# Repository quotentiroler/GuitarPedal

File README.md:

## Resurrected random guitar pedal project

This is a resurrected version of my old guitar pedal project: a digital
guitar pedal built around an RP2354A and a TI audio codec, with all the
effects done in software on a core of its own.

It went through a phase with a little OLED screen and a couple of rotary
encoders on it, and that's gone now.  Editing seventeen effects through a
128x128 screen and two knobs was never going to be pleasant, and I'm not
exactly known for my mad UI designing skillz, so the pedal itself is down
to one knob and one stomp switch and the deep editing happens somewhere
that already has a screen: there's a web app that talks to it over USB
MIDI from a browser.

So what's in here:

 - `Hardware` has the kicad files.
 - `Effects` has the seventeen effects, one file each.  They are up here
   rather than inside the firmware because three different things are
   built from them: the firmware, the test bench, and the web app's
   controls.
 - `Audio` has the DSP the effects are built out of - biquads, envelope
   followers, LFOs - and the audio loop itself.  The bench compiles the
   same files, so what gets measured is the pedal's own arithmetic.
 - `Firmware` is the rest of what runs on the pedal: USB, MIDI, scenes,
   the board pin maps.
 - `WebMIDI` is the web app that edits it.
 - `scripts` is what the build runs - the effect generator, the math
   tables, and the checks that refuse a firmware image doing something
   the audio core shouldn't.
 - `Validation` is the test suite.  Some of it runs on your machine and
   some of it wants a pedal plugged in.
 - `Documentation` remains a very optimistic name for a directory.

## Firmware

I've only ever built the firmware on Linux, but it *should* be perfectly
possible to build on MacOS or Windows too if you just figure out the
platform requirements. The project depends on the `pico-sdk` and
`tinyusb` libraries, and has submodules for both, so they get built
automatically, but the build tools your platform has to provide.

Regardless of platform, you'll need the basics:
 - git
 - make
 - python3
 - cmake

and a 32-bit arm cross-build environment.  On Linux, that would be
something like
 - arm-none-eabi-binutils-cs
 - arm-none-eabi-gcc-cs
 - arm-none-eabi-newlib

There's more than one board this can be built for, and the build won't
guess.  You say which one this tree is about once, in
`board.local`, and it stays said - it's a file rather than a
cmake cache variable specifically so that blowing away `build/` doesn't
silently change your mind for you.  So:
```
	git clone https://github.com/torvalds/GuitarPedal.git
	cd GuitarPedal
	echo unified > board.local
	make prep
	make
```
`unified` is the current one-board pedal.  The other is `split`, which is
the older modular pair of boards.  If you forget this step the configure
will stop and tell you, which is the intended behaviour - a wrong board
should be an error you fix once, not a working build for hardware you
don't have.

That gets you `build/pedal-unified.uf2` (and `.elf`, and `.bin`).  Every
artifact is named for the board it's for, so there is deliberately no
`pedal.uf2` to grab by mistake.  You can build the other board without
changing what the tree is about - ``make split`` - or both with ``make
all-boards``.

To get the `.uf2` onto the pedal you need it in BOOTSEL mode, and there
are two ways.  If it's running and plugged in, send it MIDI CC 20 with
value 126 and it will reboot into BOOTSEL on its own:
```
	amidi -l                          # find which card the pedal is
	amidi -p hw:5,0 -S "B0 14 7E"     # ...and that 5 is mine, not yours
```
Otherwise, hold the knob in while you plug it in.  The rotary encoder's
switch doubles as BOOTSEL on this board - through a Schottky, so that
QSPI traffic can't fake pulling it low - and that's the route that still
works on a pedal too broken to enumerate.  The older boards had a proper
BOOTSEL button, but it was on the little MCU daughtercard, which is fine
on a bench and useless the moment the thing is screwed into a box.

Either way a USB mass storage device shows up and you copy the file to
it.

If you have installed picotool with USB support (the pico-sdk build only
builds a cut-down version without it), you can skip all that and just do
``make flash``, which builds and flashes the board in `board.local`.
``make flash-split`` does the other one.

### Testing

`Validation` has the test suite, and it's split by what it needs.

``make check`` runs the part that needs no hardware at all: the MIDI
packetiser, whether the web app still loads and still draws the right
conclusions, and a sweep that asks every biquad in the pedal where it
actually landed.  ``make check-biquad`` is that last one on its own, and
``make check-effects`` puts signals through the effects themselves.

That last one works because of `Validation/bench`, which builds the
pedal's actual audio core - the same `single_sample()`, the same effect
headers, the same compiler flags - as a program on your machine that
takes float samples on stdin and hands them back on stdout.  It is not a
model of the signal path.  It's the signal path, with the two register
blocks the audio core touches replaced by ordinary memory.

``make check-analysis`` is the other host-only one, and it is what keeps
the per-effect pages under `Documentation/effects` honest: every curve on
those pages is a measurement, and this re-measures and says when one has
stopped being true.  It is separate from ``check`` because it re-runs
every sweep on every page, which is slow.

Then there are the ones that want hardware: ``make check-hw`` with a
signal generator, ``make check-analog`` with a patch cable from the
pedal's output back to its own input, ``make check-bench`` to ask whether
a real board agrees with the host build, and ``make check-loop`` if you
have two pedals to patch into each other.

`Validation/diagnose.py` is the odd one out, because it measures
something that isn't the pedal.  With an analog pedal in the loop it asks
which *component* of that pedal disagrees with the netlist in
`Validation/spice`, rather than only that something does - every
single-component fault the netlist could have is simulated, and the one
that best explains the measurement wins.  The ranking is
[netfault](https://github.com/quotentiroler/netfault), which has to be
installed separately; the method is a fault dictionary and is older than
any of this, the survey being Bandler and Salama, Proc. IEEE 73 (1985).

It asks at several drive levels rather than sweeping once.  [RAT]'s clamp
is a logarithm, so the part that decides where it folds does nothing at
all until the drive reaches it, and a single sweep cannot tell a wrong
one from a right one - it ranks on the noise instead and does not say so.
That costs what it sounds like: an ngspice transient is about 1.8s, so a
dictionary over the whole netlist is a couple of hours.  It is built once
for a board and matched in milliseconds after that.

Nothing here has been run against a physical board yet.  Every number it
has produced so far came from a fault injected into the netlist and
handed back to it, which says the arithmetic works and says nothing about
whether a real measurement is clean enough.

## Hardware

The kicad design files (and some supporting infrastructure, like the 3D
printed insert and the enclosure drill rules) are in the ``Hardware``
subdirectory.

These days it's just the one board.  `Hardware/usb-stomp` has the RP2354A
and the TI TAC5242 codec sitting directly on it, and that's the whole
pedal: no cable, no daughtercards, no connectors in between.

What's on it:

 - a 1/4" input jack and a 1/4" output jack
 - a third 1/4" jack for an expression pedal or a remote stomp switch
 - MIDI in and out, on 3.5mm "Type A" TRS jacks (out through a 5V
   buffer, in through an optocoupler, like MIDI has always wanted)
 - USB-C, and the usual 9V guitar pedal power jack
 - one rotary encoder with a switch under it, and one stomp switch
 - three addressable WS2812B LEDs

The MIDI jacks and the expression jack are the genuinely new things.  The
older boards had nowhere to put them - the expression jack in particular
wants two ADC pins, and those are exactly the pins the old MCU board was
spending on hardware MIDI, so it could not have existed there at all.

Fair warning on that expression jack, though: the hardware is done and
the firmware can read it, but only when the host asks it to over SysEx.
Right now it's a probe for figuring out what people actually plug in
there - expression pedals don't even agree on which contact is the wiper
- and nothing is wired up to *do* anything with the result yet.

### How it used to be

It used to be modular, and those board files are all still here.  There
were two little daughtercards for the "core" hardware - the RP2354
microcontroller (`Hardware/rp2354`) and the TI TAC5112 codec
(`Hardware/codec`) - plus a board for the audio and 9V DC power jacks
(`Hardware/audio-jacks`), and a main board (`Hardware/pedal-board`) for
the pedal IO: i2c connector for the screen, USB-C programming port,
rotary encoders, pin header for stomp switches.  The two halves were
joined by a 12P 0.5mm FFC cable carrying power and data lines (i2c for
control, i2s for audio).

That was mostly so I could try out different form factors.  It let me lay
the two halves out independently, and it was flexible enough to cram a
125B enclosure full of jacks, rotaries and the screen all in one top
area.  There was also a worry about noise isolation, which in the end
never had to be tested.

I used the nice HiRose BM28 series connectors on the modular boards.
They are absolutely tiny, which makes for a great board footprint but
admittedly also makes for a slightly more complicated board due to the
tiny 0.35mm pitch.  I'm not a fan of the traditional pin headers simply
because they make it so hard to do compact form factors.

Those boards are finished and they still work - the firmware builds for
them, and they're still useful for testing.  But what this section used
to say was that if you know what you want, you should just put the codec
directly on the audio jack board and the rp2354 on the IO board.  Which,
yes.  That's the board above.

### Images

The bare `usb-stomp` board, powered up.

## Basic UI

There's no screen.  The pedal has one knob, one footswitch and three
LEDs, and everything else happens in a browser.

### On the pedal

Out of the box the footswitch is bypass - tap for in-circuit or not, hold
it for the tuner - and the knob is the master volume, with either kind of
press on it putting the volume back where it started.  That last one
sounds trivial and isn't: it's the way back when you can't see anything.

But none of that is compiled in.  There are five gestures - turn the
knob, tap it, hold it, tap the switch, hold the switch - and what each
one means is a table the pedal looks up and the app writes.  You can
point the knob at any parameter of any effect, or make a single press
take one effect's mix up while it takes another's down.  A pedal with no
screen can't tell you what its knob is for, so that has to be settable
from something that can.

The three LEDs, left to right: something is wrong (red for clipping,
amber for dropped samples), in circuit or bypassed, and the chain is
busy - where "busy" means whatever the effect thinks it means, so the
gate lights it while it's gating and the compressor while it's
compressing.

### In the browser

`WebMIDI` is a static web page that talks to the pedal over USB
MIDI.  There's nothing to install and it runs off a phone.

It doesn't know what the effects are.  It asks.  The pedal describes
every effect it has - every pot, the ranges, the units, the hover text -
and the app builds itself out of that, so it can't drift out of step with
the firmware, and adding an effect to the pedal makes it show up in the
app without touching the app.

What you actually do there is *route*.  There are seventeen effects and
none of them are in your signal path until you say so: routing picks
which ones run, and in what order, and the order is yours, because a
boost in front of a delay is a different pedal from a delay in front of a
boost.  Whatever you don't route costs nothing.

Pots are mostly just numbers, except where they aren't - the tone stacks,
the parametric EQ and the cab sim draw their actual frequency response,
so you can see the curve instead of inferring it from three knob
positions.

A tone stack with a 10dB mid bump at 810Hz and a tape echo behind it, and
the fifteen effects that aren't routed sitting at the bottom waiting to
be.  The faint grey line is the phase response.

Eight scenes fit in the pedal's own flash.  A scene is a routing plus
everything set inside it, and a MIDI program change recalls one, which is
half of what those MIDI jacks are for: a cheap footswitch can step
between scenes with no computer in sight.

## Audio effects

Seventeen of them, plus three that are always there and can't be
unrouted: the **Signal Chain** at the front, which is the input trim, the
noise gate and the master volume
([measured](Documentation/effects/signal-chain.md)), and behind them the
**Settings**, which is USB audio routing, MIDI channel, LED brightness
and what the tuner is tuning to, and the **Expression Jack**, which is
what is plugged into it and where that thing's travel ends.

They're listed in the order they run in by default.  This is an overview
and not documentation - the app is the reference, because it gets the
ranges, the units and the hover text from the pedal itself rather than
from anything I typed here.

 - **Tone** - bass, mid and treble, with the corner frequencies
   adjustable and the mid's Q as well.  There are two of them, so one
   can go in front of a distortion and one behind it.
 - **Preamp** - a two-stage 12AX7 model, class-A biased with the
   asymmetry left in, and a JFET stage after it.
 - **Compressor** - level, ratio, attack, release, and a boost, so it
   can also just be a clean boost when that's what you want.  The
   threshold reaches low enough to work on a quiet pickup with nothing
   in front of it.  [Measured](Documentation/effects/compressor.md).
 - **Boost**, with distortion.  I like this one.  Others may not.  Set
   the boost stupidly high and the level low, and instead of clipping at
   the level the signal *folds* back down, which gives you harmonics
   that a soft or hard clipper doesn't.
 - **Klonlike** - the obvious model: 18V charge pump for headroom,
   germanium diodes, and the clean/dirty blend that tracks the gain
   knob.  Originally by Bryan Leavelle.
   [Measured](Documentation/effects/klon.md).
 - **Rat Sketch** - a ProCo RAT, from the Aion FX Helios clone.  One
   op-amp with up to 67dB and several decibels an octave of treble
   emphasis inside the feedback, then diodes to ground, then the one
   backwards Filter knob.  Three clipping modes, because the pedal has
   three.  The op-amp saturates inside its own loop and the diodes are
   solved rather than approximated, which is where its second harmonic
   comes from.  [Measured](Documentation/effects/rat.md).
 - **Phaser**, **Flanger** and **Vibrato** - the modulation three.  All
   simple, all a delay line and an LFO wearing different hats.
 - **Tape Echo** - the Echo King from Cleveland Music Co, a model of the
   Maestro Echoplex tape delays, converted from the Hothouse examples.
   All credit to Ricky Sheaves, and blame me for the conversion.
 - **Reverb** - comb filters into allpasses, the traditional way.
   [Measured](Documentation/effects/reverb.md).
 - **Pitch** - not the clever FFT kind.  It walks a delay line faster or
   slower than real time in two phases, crossfaded with a sine so the
   wrap doesn't click.  So it shifts *and* delays, and it feeds back into
   itself, which makes it a short echo that shifts again on every repeat.
   Most natural an octave up, but it does fractions.
 - **Tremolo** - amplitude modulation, several shapes.
 - **Parametric EQ** - five bands, two shelves and three peaks, every one
   of them tunable across the whole range.
 - **Frenchie Amp** - a small amp: triode, tone stack, power amp.
 - **Test Tone** - sine, triangle, saw or noise at a known level and
   frequency.  It replaces the input rather than adding to it, which is
   what lets the pedal measure itself.
 - **Cabinet** - a speaker cone as a moving mass rather than as a filter,
   integrated at the sample rate.  Pick one of five cabinets and it knows
   the rest of itself; the knobs are how hard the amp drives it, how much
   the amp lets its resonance bloom, and where the mic is pointed.

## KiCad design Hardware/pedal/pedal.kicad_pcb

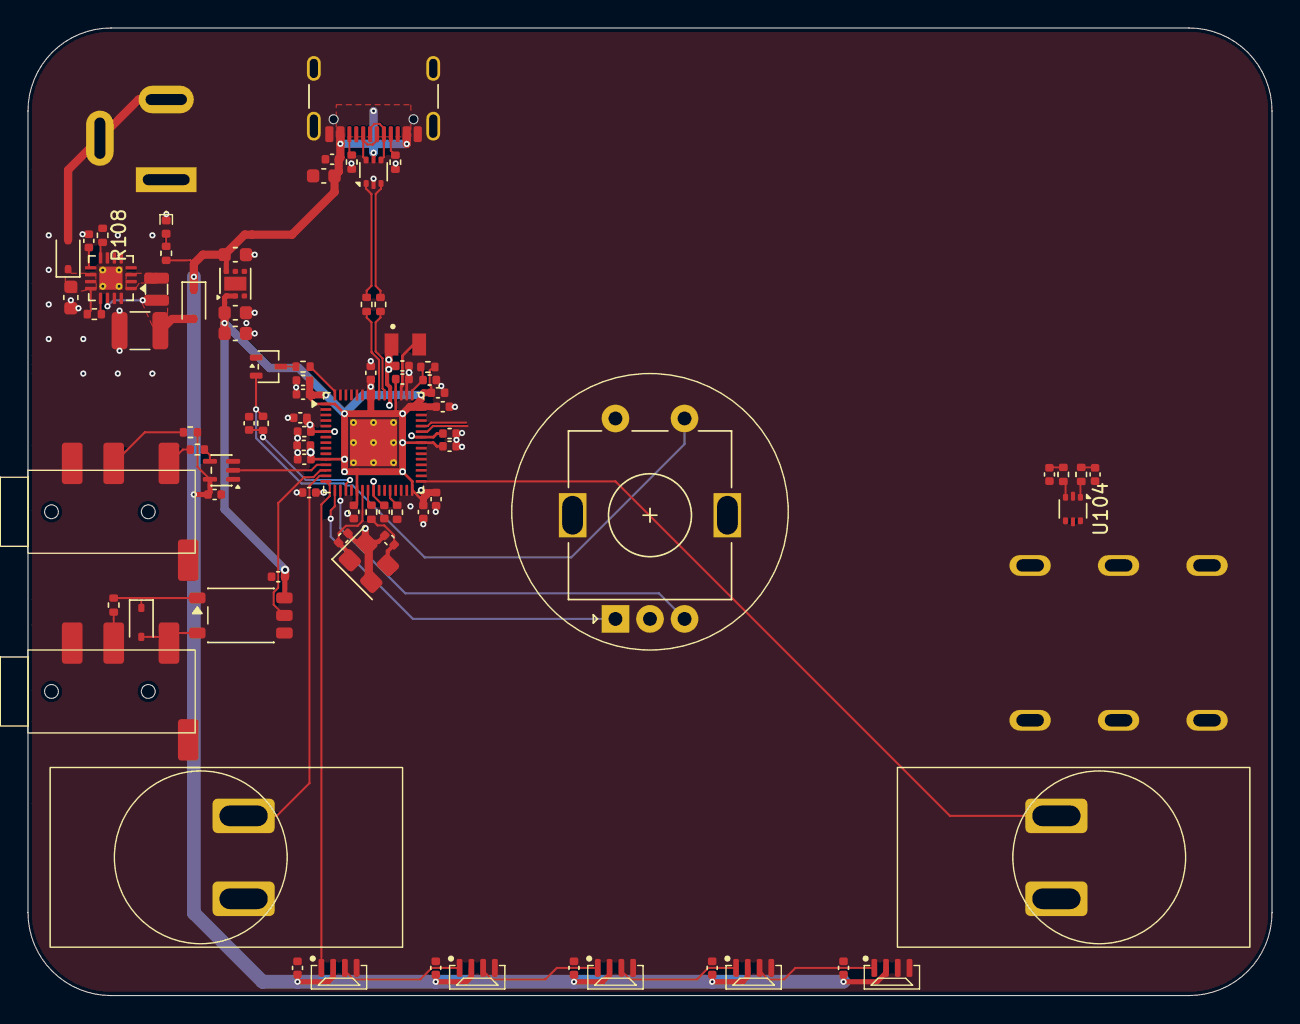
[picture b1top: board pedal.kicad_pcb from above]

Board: 4 copper layers, 90.0 x 70.0 mm, 84 parts (0 on the bottom side), 53 nets.

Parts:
C101, C110, C201, C202, C203, C204, C205, C206, C207, C405, C407, C408, C409, C410, C411, C412, C413, C415, C417: 0.1uF; C_0402_1005Metric
C102, C103: 10uF; C_0603_1608Metric
C104: 22uF; C_1210_3225Metric
C105, C108: 22nF; C_0402_1005Metric
C106: 2.2nF; C_0402_1005Metric
C107, C109, C111: 2.2uF; C_0603_1608Metric
C401, C402, C403, C406, C414, C416, C418, C421, C422: 4.7uF; C_0402_1005Metric
C419, C420: 15pF; C_0402_1005Metric
D102: LED; LED_0402_1005Metric
D103, D104, D201: 1N5819WS; D_SOD-323
D106: BAT54SW; SOT-323_SC-70
D202, D203, D204, D205, D206: WS2812B-4020
J101: USB_C_Receptacle_USB2.0_16P; USB_C_Receptacle_GCT_USB4105-xx-A_16P_TopMnt_Horizontal
J102: Barrel_Jack_Switch; Wurth WR-DC 2.1mm Power Jack
J103: AudioJack3_SwitchTR; NRJ6HM-1-PRE
J201, J202: AudioJack4; PJ-320D
L101: 2.2uH; L_0806
L401: 3.3uH; AOTA-B2016
R101, R102: 5k1; R_0402_1005Metric
R103, R104, R106, R107: 1k; R_0402_1005Metric
R105, R108: 100k; R_0402_1005Metric
R201, R202, R203: 220; R_0402_1005Metric
R402, R405, R406: 33Ω; R_0402_1005Metric
R403: 2.2kΩ; R_0402_1005Metric
R404, R407: 1kΩ; R_0402_1005Metric
SW101, SW102: SW_SPST; Daier PBS-24B-2
SW103: RotaryEncoder_Switch_MP; RotaryEncoder_EC11-Switch_Vertical_H20mm
U101, U104: USBLC6-2P6; SOT-666
U102: TPS62153; VQFN-16-1EP_3x3mm_P0.5mm_EP1.68x1.68mm_ThermalVias
U103: TLV76733DRVx; WSON-6-1EP_2x2mm_P0.65mm_EP1x1.6mm
U201: SN74AHCT1G125DCKR; SOT-353_SC-70-5
U202: TLP2310; SO-5-6_4.55x3.7mm_P1.27mm
U402: RP2354A; QFN-60-1EP_7x7mm_P0.4mm_EP3.4x3.4mm_ThermalVias
Y401: ABM8-272-T3; Crystal_SMD_3225-4Pin_3.2x2.5mm

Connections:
+1V1: C402.1, C403.1, C405.1, C407.1, C408.1, L401.1, U402.6 (DVDD), U402.23 (DVDD), U402.39 (DVDD), U402.50 (VREG_FB)
+3V3: C109.1, C111.1, C202.2, C401.1, C409.1, C410.1, C411.1, C412.1, C413.1, C414.1, C415.1, C416.1, C417.1, C418.1, C421.1, C422.1, R402.1, U103.1 (OUT), U103.2 (SNS), U104.5 (VBUS), U202.6 (VDD), U402.1 (IOVDD), U402.11 (IOVDD), U402.20 (IOVDD), U402.30 (IOVDD), U402.38 (IOVDD), U402.44 (ADC_AVDD), U402.45 (IOVDD), U402.49 (VREG_VIN), U402.53 (USB_OTP_VDD), U402.54 (QSPI_IOVDD)
+9V: C103.1, D103.1 (K), R105.1, U102.10 (VIN), U102.11 (VIN), U102.12 (VIN)
/BOOTSEL: D106.3 (COM), R403.1
/DEF: R108.2, U102.8 (DEF)
/EN: R105.2, U102.13 (EN)
/MIDI/MIDI_IN: J201.R1, R201.1
/MIDI/MIDI_OUT: J202.T, R203.2
/RP2354/ADC0: C105.1, R104.1, U402.40 (GPIO26_ADC0)
/RP2354/ADC1: C108.1, R106.1, U402.41 (GPIO27_ADC1)
/RP2354/GPIO8: U201.2, U402.12 (GPIO8)
/RP2354/GPIO9: U202.5 (VO), U402.13 (GPIO9)
/RP2354/GPIO10: SW102.2 (B), U402.14 (GPIO10)
/RP2354/GPIO11: D202.1 (DIN), U402.15 (GPIO11)
/RP2354/GPIO12: SW103.A, U402.16 (GPIO12)
/RP2354/GPIO13: SW103.B, U402.17 (GPIO13)
/RP2354/GPIO14: C110.2, R107.2, U402.18 (GPIO14)
/RP2354/GPIO19: SW101.1 (A), U402.31 (GPIO19)
/RP2354/VREG_AVDD: C406.1, R402.2, U402.46 (VREG_AVDD)
/RP2354/VREG_LX: L401.2, U402.48 (VREG_LX)
/RP2354/XIN: C419.1, U402.21 (XIN), Y401.1
/RP2354/XOUT: R407.1, U402.22 (XOUT)
/SS: C106.2, U102.9 (SS/TR)
/SW: L101.1, U102.1 (SW), U102.2 (SW), U102.3 (SW)
/USB-D+: R405.2, U101.1 (I/O1)
/USB-D-: R406.2, U101.3 (I/O2)
/USBCONN-D+: J101.A6 (D+), J101.B6 (D+), U101.6 (I/O1)
/USBCONN-D-: J101.A7 (D-), J101.B7 (D-), U101.4 (I/O2)
/VOS: C104.1, D104.2 (A), L101.2, U102.14 (VOS)
GND: C101.1, C102.2, C103.2, C104.2, C105.2, C106.1, C107.2, C108.2, C109.2, C110.1, C111.2, C201.1, C202.1, C203.1, C204.1, C205.1, C206.1, C207.1, C401.2, C402.2, C403.2, C405.2, C406.2, C407.2, C408.2, C409.2, C410.2, C411.2, C412.2, C413.2, C414.2, C415.2, C416.2, C417.2, C418.2, C419.2, C420.2, C421.2, C422.2, D102.1 (K), D202.4 (VSS), D203.4 (VSS), D204.4 (VSS), D205.4 (VSS), D206.4 (VSS), J101.A1 (GND), J101.A12 (GND), J101.B1 (GND), J101.B12 (GND), J101.SH (SHIELD), J102.1, J103.RN, J103.S, J103.TN, J202.S, R101.2, R102.2, SW101.2 (B), SW102.1 (A), SW103.C, SW103.MP, SW103.S2, U101.2 (GND), U102.5 (FB), U102.6 (GND), U102.7 (FSW), U102.15 (GND), U102.16 (GND), U102.17 (GND), U103.3 (GND), U103.5 (GND), U103.7 (PAD), U104.2 (GND), U201.1, U201.3 (GND), U202.4 (GND), U402.47 (VREG_PGND), U402.61 (GND), Y401.2 (G), Y401.4 (G)
unnamed: C420.1, R407.2, Y401.3
unnamed: D102.2 (A), R103.1
unnamed: D103.2 (A), J102.2, J102.3
unnamed: D106.2 (K), R107.1, SW103.S1
unnamed: D201.2 (A), J201.T, U202.3 (K)
unnamed: D201.1 (K), R201.2, U202.1 (A)
unnamed: D202.3 (DOUT), D203.1 (DIN)
unnamed: D203.3 (DOUT), D204.1 (DIN)
unnamed: D204.3 (DOUT), D205.1 (DIN)
unnamed: D205.3 (DOUT), D206.1 (DIN)
unnamed: J101.A5 (CC1), R101.1
unnamed: J101.B5 (CC2), R102.1
unnamed: J103.R, U104.6 (I/O1)
unnamed: J103.T, U104.4 (I/O2)
unnamed: J202.R1, R202.2
unnamed: R104.2, U104.3 (I/O2)
unnamed: R106.2, U104.1 (I/O1)
unnamed: R203.1, U201.4
unnamed: R403.2, U402.60 (QSPI_SS)
unnamed: R404.2, U402.26 (RUN)
unnamed: R406.1, U402.51 (USB_DM)
unnamed: R405.1, U402.52 (USB_DP)
VBUS: C101.2, C102.1, C107.1, C201.2, C203.2, C204.2, C205.2, C206.2, C207.2, D104.1 (K), D202.2 (VDD), D203.2 (VDD), D204.2 (VDD), D205.2 (VDD), D206.2 (VDD), J101.A4 (VBUS), J101.A9 (VBUS), J101.B4 (VBUS), J101.B9 (VBUS), R103.2, R108.1, R202.1, U101.5 (VBUS), U103.6 (IN), U201.5 (VCC)
